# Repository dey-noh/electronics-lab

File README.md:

# electronics-lab
A curated collection of my KiCad PCB design projects from  schematics to layout and fabrication ready files. This repo showcases personal experiments, functional circuits and open  source hardware ideas.

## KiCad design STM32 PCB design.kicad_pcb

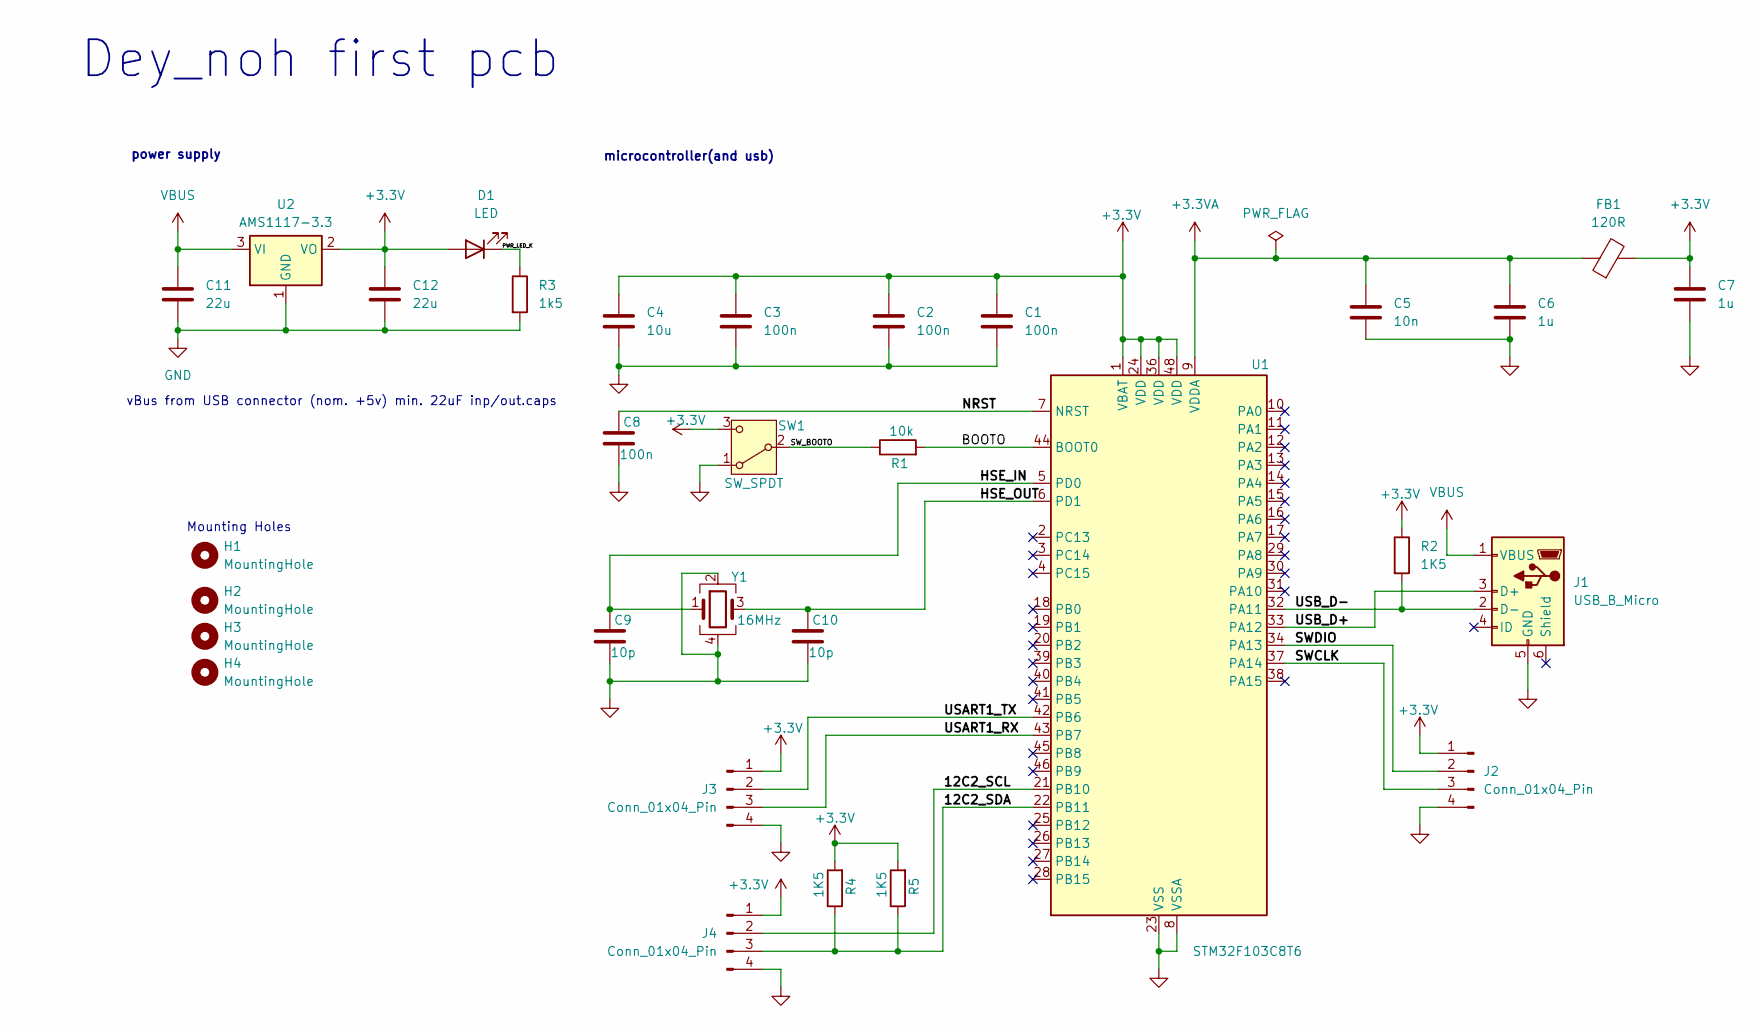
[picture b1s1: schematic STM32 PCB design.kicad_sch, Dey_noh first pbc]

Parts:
C1, C2, C3, C8: 100n; C_0402_1005Metric
C4: 10u; C_0603_1608Metric
C5: 10n; C_0402_1005Metric
C6, C7: 1u; C_0402_1005Metric
C9, C10: 10p; C_0402_1005Metric
C11, C12: 22u; C_0805_2012Metric
D1: LED; LED_0603_1608Metric
FB1: 120R; L_0603_1608Metric
H1, H2, H3, H4: MountingHole; MountingHole_2.1mm
J1: USB_B_Micro; USB_Micro-B_Wuerth_629105150521
J2, J3, J4: Conn_01x04_Pin; PinHeader_1x04_P2.54mm_Vertical
R1: 10k; R_0402_1005Metric
R2, R4, R5: 1K5; R_0402_1005Metric
R3: 1k5; R_0402_1005Metric
SW1: SW_SPDT; SW_CK_JS202011AQN_DPDT_Angled
U1: STM32F103C8T6; LQFP-48_7x7mm_P0.5mm
U2: AMS1117-3.3; SOT-223-3_TabPin2
Y1: 16MHz; Crystal_SMD_3225-4Pin_3.2x2.5mm

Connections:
+3.3V: C1.1, C2.1, C3.1, C4.1, C7.1, C12.1, D1.2 (A), FB1.2, J2.1, J3.1, J4.1, R2.1, R4.2, R5.2, SW1.3 (C), U1.1 (VBAT), U1.24 (VDD), U1.36 (VDD), U1.48 (VDD), U2.2 (VO)
+3.3VA: C5.1, C6.1, FB1.1, U1.9 (VDDA)
/12C2_SCL: J4.2, U1.21 (PB10)
/12C2_SDA: J4.3, R4.1, R5.1, U1.22 (PB11)
/BOOTO: R1.2, U1.44 (BOOT0)
/HSE_IN: C9.1, U1.5 (PD0), Y1.1
/HSE_OUT: C10.1, U1.6 (PD1), Y1.3
/NRST: C8.1, U1.7 (NRST)
/PWR_LED_K: D1.1 (K), R3.1
/SWCLK: J2.3, U1.37 (PA14)
/SWDIO: J2.2, U1.34 (PA13)
/SW_BOOTO: R1.1, SW1.2 (B)
/USART1_RX: J3.3, U1.43 (PB7)
/USART1_TX: J3.2, U1.42 (PB6)
/USB_D+: J1.3 (D+), U1.33 (PA12)
/USB_D-: J1.2 (D-), R2.2, U1.32 (PA11)
GND: C1.2, C2.2, C3.2, C4.2, C5.2, C6.2, C7.2, C8.2, C9.2, C10.2, C11.2, C12.2, J1.5 (GND), J2.4, J3.4, J4.4, R3.2, SW1.1 (A), U1.8 (VSSA), U1.23 (VSS), U1.35 (VSS), U1.47 (VSS), U2.1 (GND), Y1.2, Y1.4
VBUS: C11.1, J1.1 (VBUS), U2.3 (VI)

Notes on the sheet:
Mounting Holes
microcontroller(and usb)
vBus from USB connector (nom. +5v) min. 22uF inp/out.caps
Dey_noh first pcb
power supply

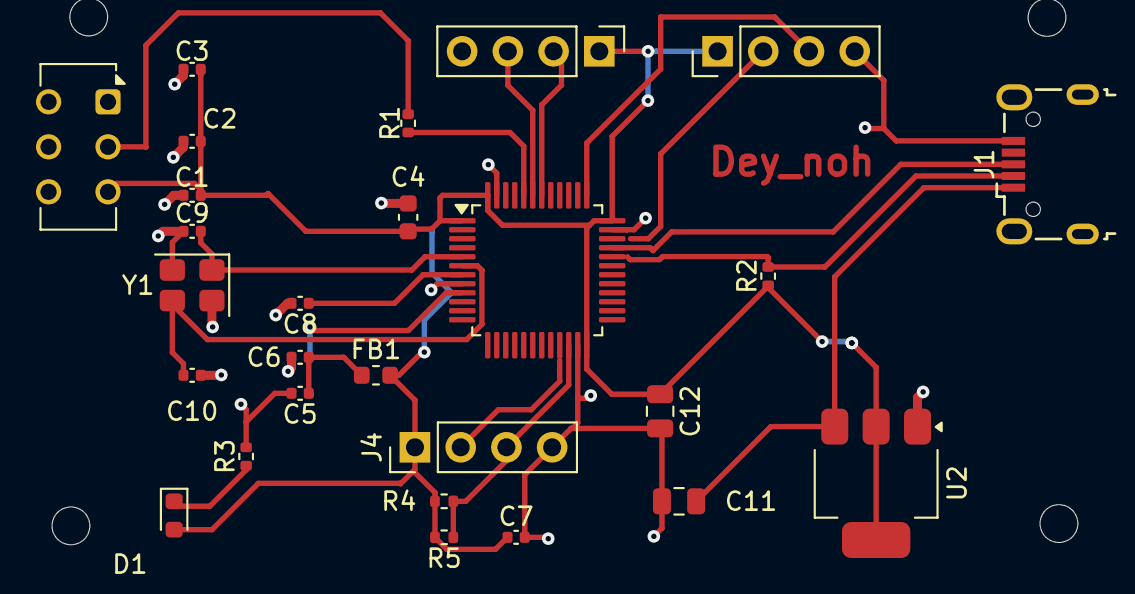
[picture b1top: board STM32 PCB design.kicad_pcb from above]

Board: 2 copper layers, 31 parts (0 on the bottom side), 18 nets.
